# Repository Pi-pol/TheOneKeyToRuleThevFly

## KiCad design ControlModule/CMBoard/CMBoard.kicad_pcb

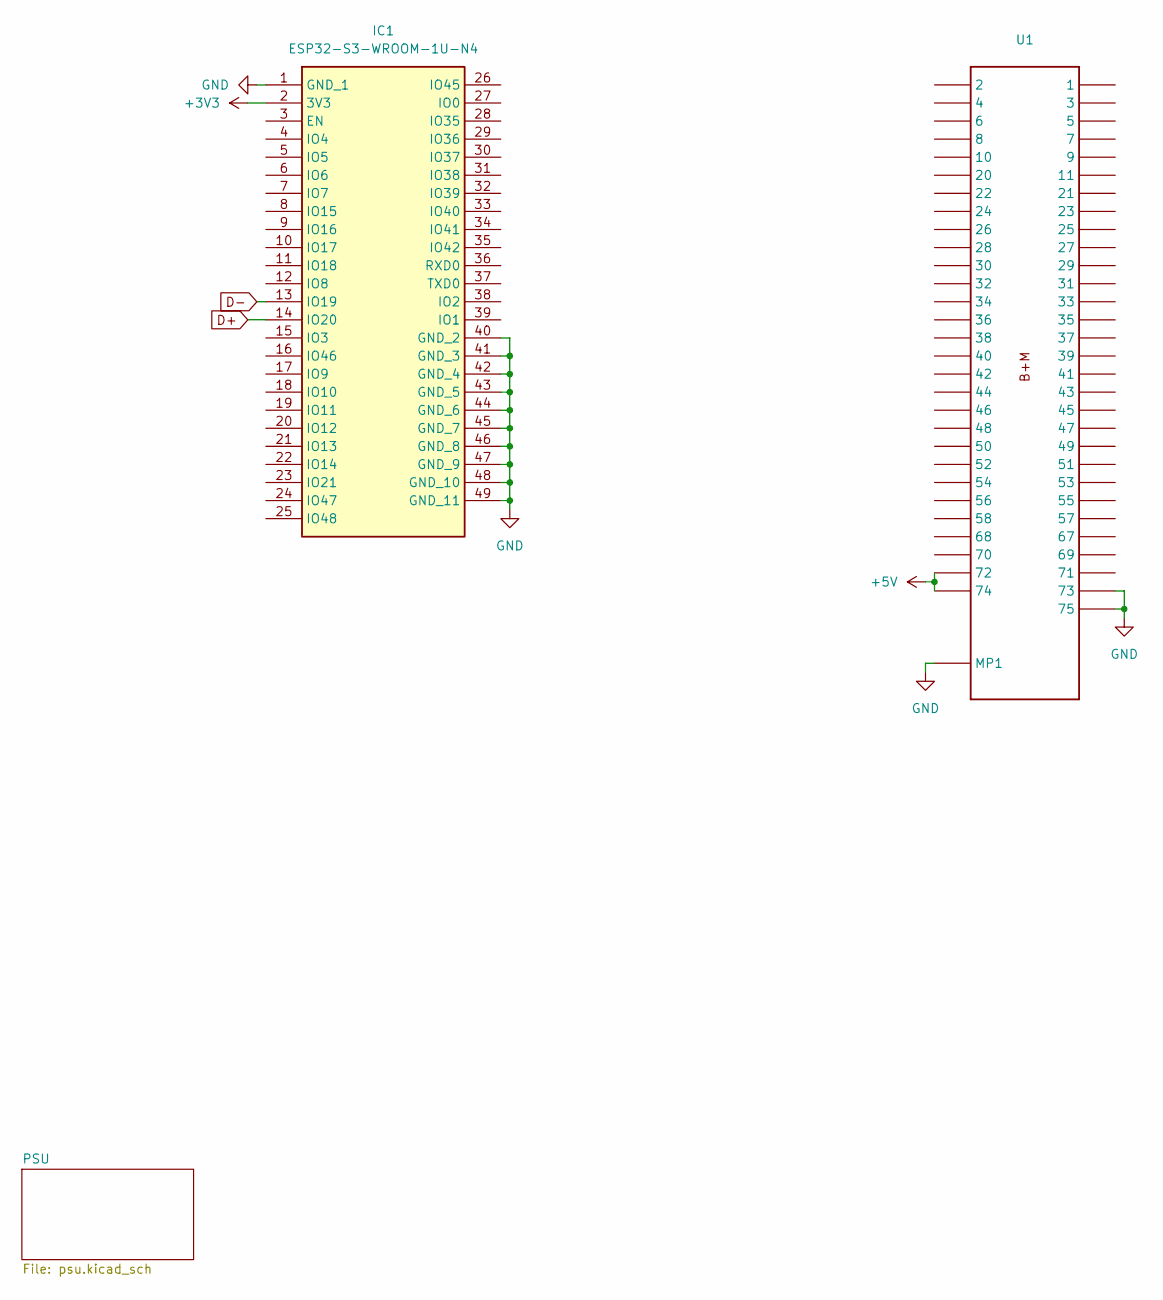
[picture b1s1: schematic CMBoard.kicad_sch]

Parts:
IC1: ESP32-S3-WROOM-1U-N4; ESP32S3WROOM1UN4; Manufacturer_Part_Number ESP32-S3-WROOM-1U-N4; Mouser Part Number 356-ESP32S3WROOM1UN4
U1: B+M 2280

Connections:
+3V3: IC1.2 (3V3); also elsewhere on the board
+5V: U1.P$72 (72), U1.P$74 (74); also elsewhere on the board
D+: IC1.14 (IO20); also elsewhere on the board
D-: IC1.13 (IO19); also elsewhere on the board
GND: IC1.1 (GND_1), IC1.40 (GND_2), IC1.41 (GND_3), IC1.42 (GND_4), IC1.43 (GND_5), IC1.44 (GND_6), IC1.45 (GND_7), IC1.46 (GND_8), IC1.47 (GND_9), IC1.48 (GND_10), IC1.49 (GND_11), U1.MP1, U1.P$73 (73), U1.P$75 (75); also elsewhere on the board

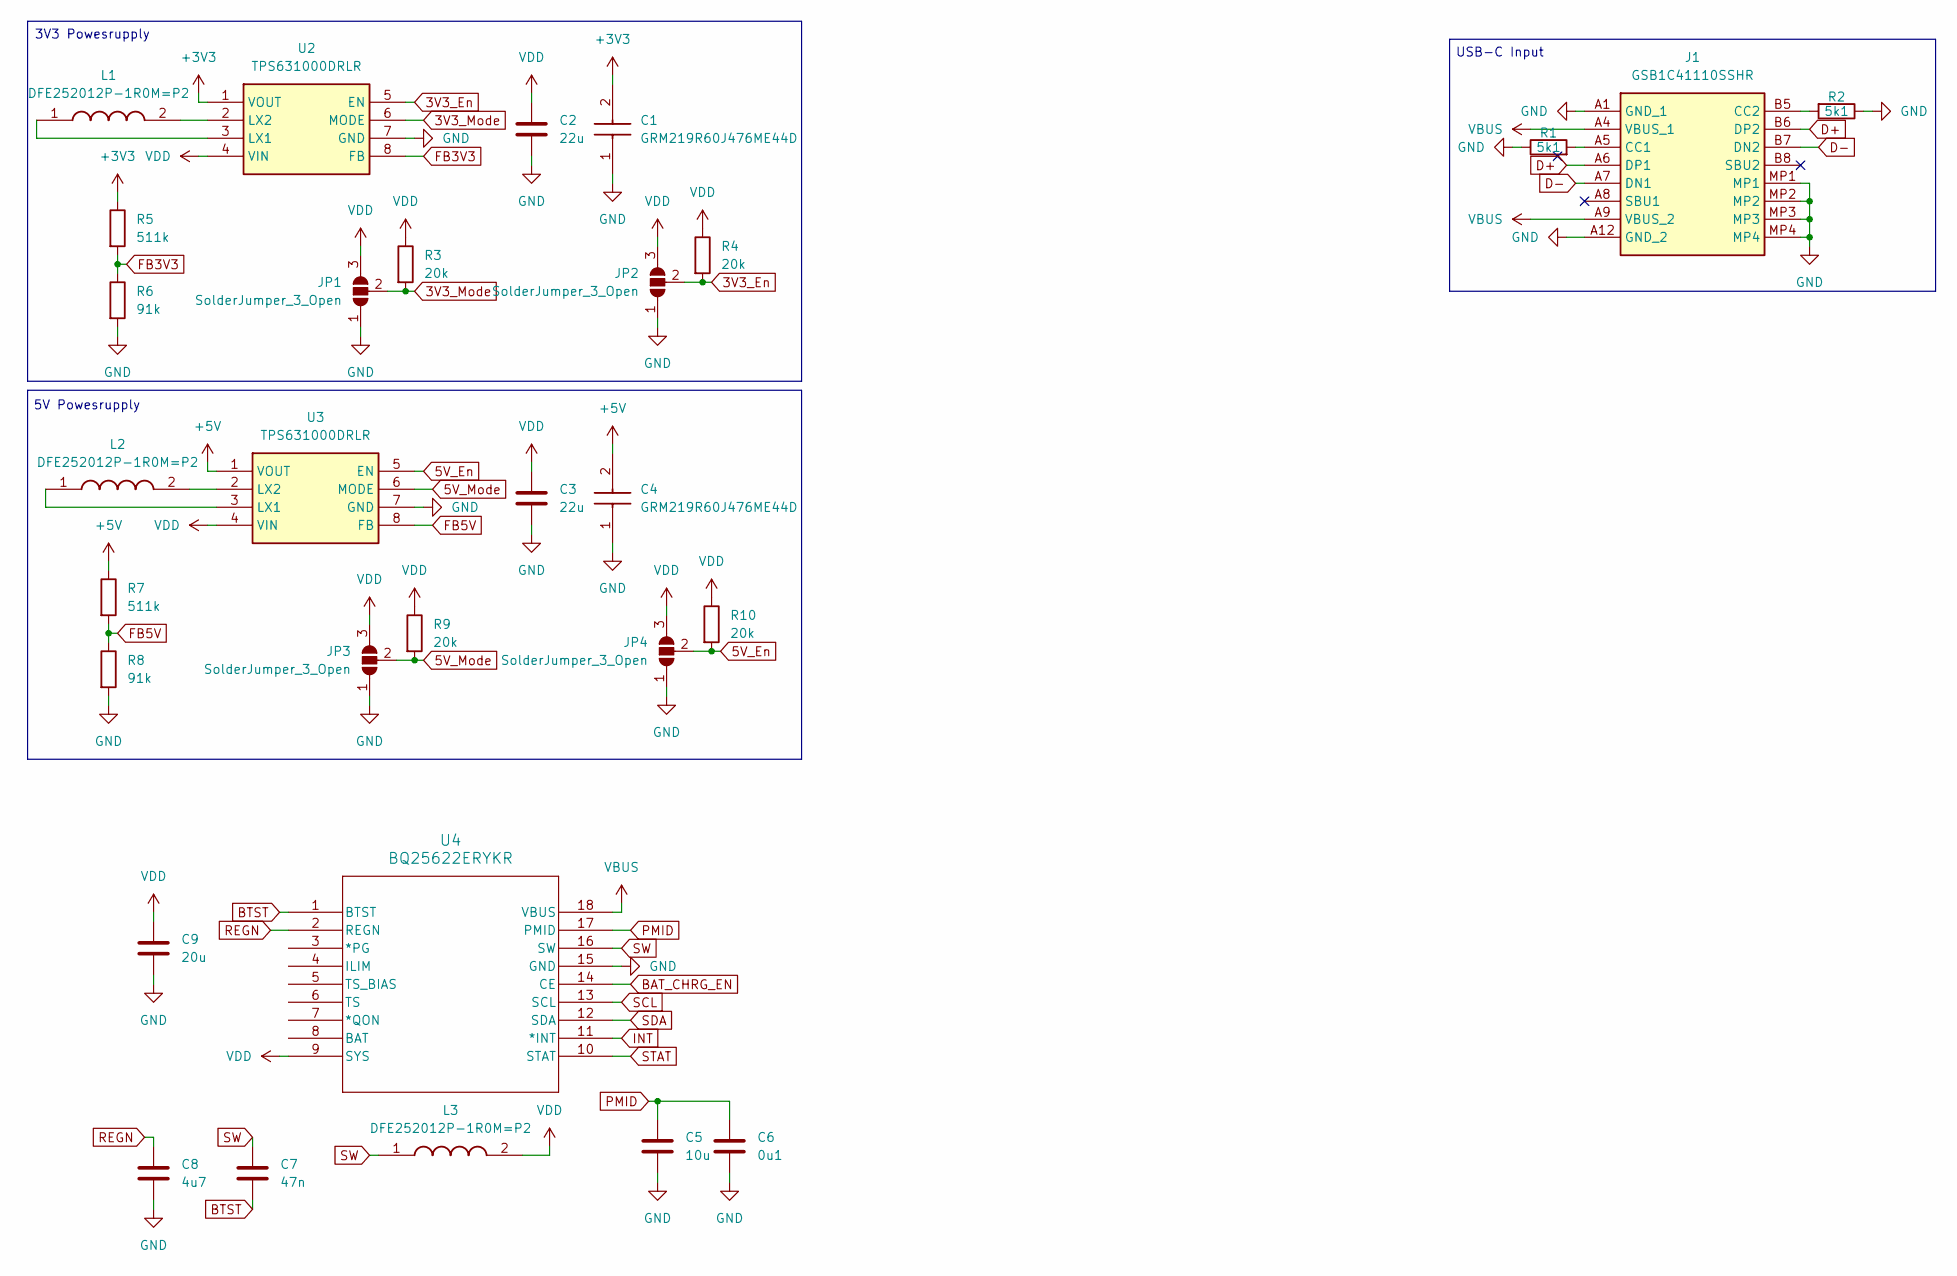
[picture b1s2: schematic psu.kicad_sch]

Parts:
C1, C4: GRM219R60J476ME44D; GRM21BR60J226ME39L; Manufacturer_Part_Number GRM219R60J476ME44D; Mouser Part Number 81-GRM219R60J476ME4D
C2, C3: 22u; C_0603_1608Metric
C5: 10u; C_0603_1608Metric
C6: 0u1; C_0603_1608Metric
C7: 47n; C_0603_1608Metric
C8: 4u7; C_0603_1608Metric
C9: 20u; C_0603_1608Metric
J1: GSB1C41110SSHR; Manufacturer_Part_Number GSB1C41110SSHR
JP1, JP2, JP3, JP4: SolderJumper_3_Open; SolderJumper-3_P1.3mm_Open_Pad1.0x1.5mm
L1, L2, L3: DFE252012P-1R0M=P2; DFE2HCAH1R0MJ0L; Manufacturer_Part_Number DFE252012P-1R0M=P2; Mouser Part Number 81-DFE252012P-1R0MP2
R1, R2: 5k1; R_0603_1608Metric
R3, R4, R9, R10: 20k; R_0603_1608Metric
R5, R7: 511k; R_0603_1608Metric
R6, R8: 91k; R_0603_1608Metric
U2, U3: TPS631000DRLR; SOTFL50P160X60-8N; Manufacturer_Part_Number TPS631000DRLR; Mouser Part Number 595-TPS631000DRLR
U4: BQ25622ERYKR; WQFN-HR18_RYK_TEX

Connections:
3V3_En: JP2.2 (C), R4.2, U2.5 (EN)
3V3_Mode: JP1.2 (C), R3.2, U2.6 (MODE)
5V_En: JP4.2 (C), R10.2, U3.5 (EN)
5V_Mode: JP3.2 (C), R9.2, U3.6 (MODE)
+3V3: C1.2, R5.1, U2.1 (VOUT); also elsewhere on the board
+5V: C4.2, R7.1, U3.1 (VOUT); also elsewhere on the board
BAT_CHRG_EN: U4.14 (CE)
BTST: C7.2, U4.1 (BTST)
D+: J1.A6 (DP1), J1.B6 (DP2); also elsewhere on the board
D-: J1.A7 (DN1), J1.B7 (DN2); also elsewhere on the board
FB3V3: R5.2, R6.1, U2.8 (FB)
FB5V: R7.2, R8.1, U3.8 (FB)
GND: C1.1, C2.2, C3.2, C4.1, C5.2, C6.2, C8.2, C9.2, J1.A1 (GND_1), J1.A12 (GND_2), J1.MP1, J1.MP2, J1.MP3, J1.MP4, JP1.1 (A), JP2.1 (A), JP3.1 (A), JP4.1 (A), R1.1, R2.1, R6.2, R8.2, U2.7 (GND), U3.7 (GND), U4.15 (GND); also elsewhere on the board
INT: U4.11 (*INT)
unnamed: J1.A5 (CC1), R1.2
unnamed: J1.B5 (CC2), R2.2
unnamed: L1.1, U2.3 (LX1)
unnamed: L1.2, U2.2 (LX2)
unnamed: L2.1, U3.3 (LX1)
unnamed: L2.2, U3.2 (LX2)
PMID: C5.1, C6.1, U4.17 (PMID)
REGN: C8.1, U4.2 (REGN)
SCL: U4.13 (SCL)
SDA: U4.12 (SDA)
STAT: U4.10 (STAT)
SW: C7.1, L3.1, U4.16 (SW)
VBUS: J1.A4 (VBUS_1), J1.A9 (VBUS_2), U4.18 (VBUS)
VDD: C2.1, C3.1, C9.1, JP1.3 (B), JP2.3 (B), JP3.3 (B), JP4.3 (B), L3.2, R3.1, R4.1, R9.1, R10.1, U2.4 (VIN), U3.4 (VIN), U4.9 (SYS)

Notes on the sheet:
5V Powesrupply
3V3 Powesrupply
USB-C Input

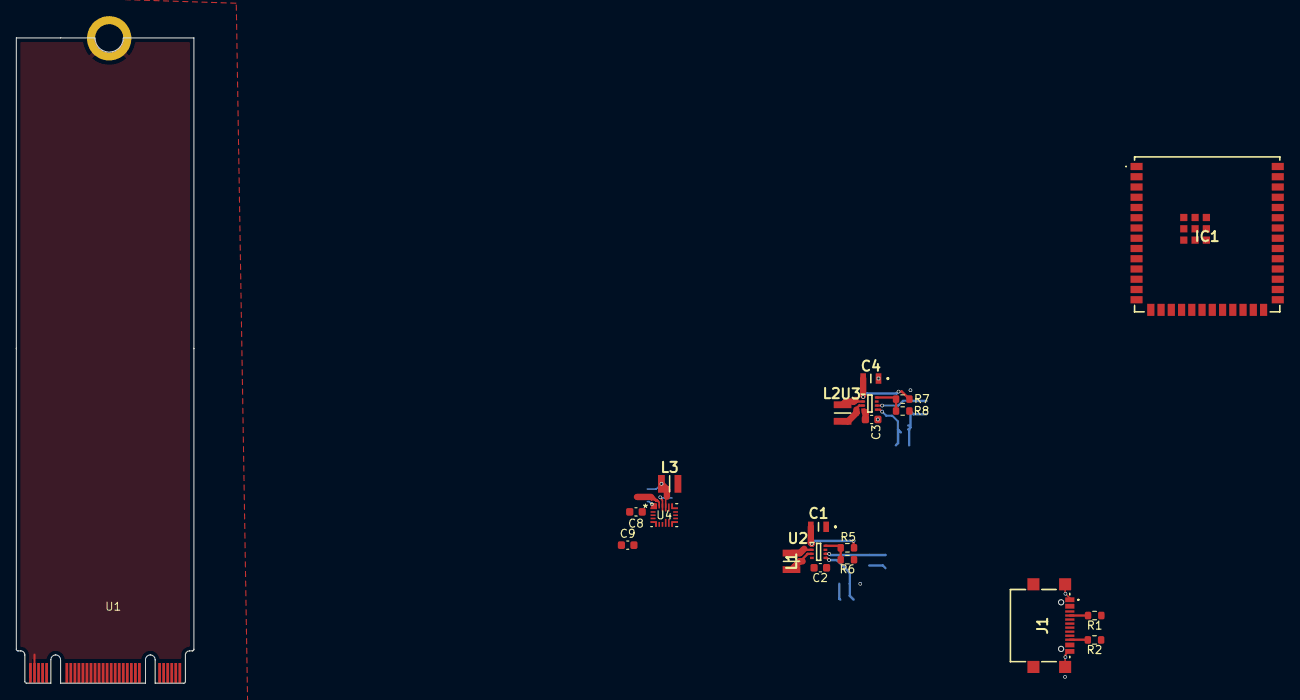
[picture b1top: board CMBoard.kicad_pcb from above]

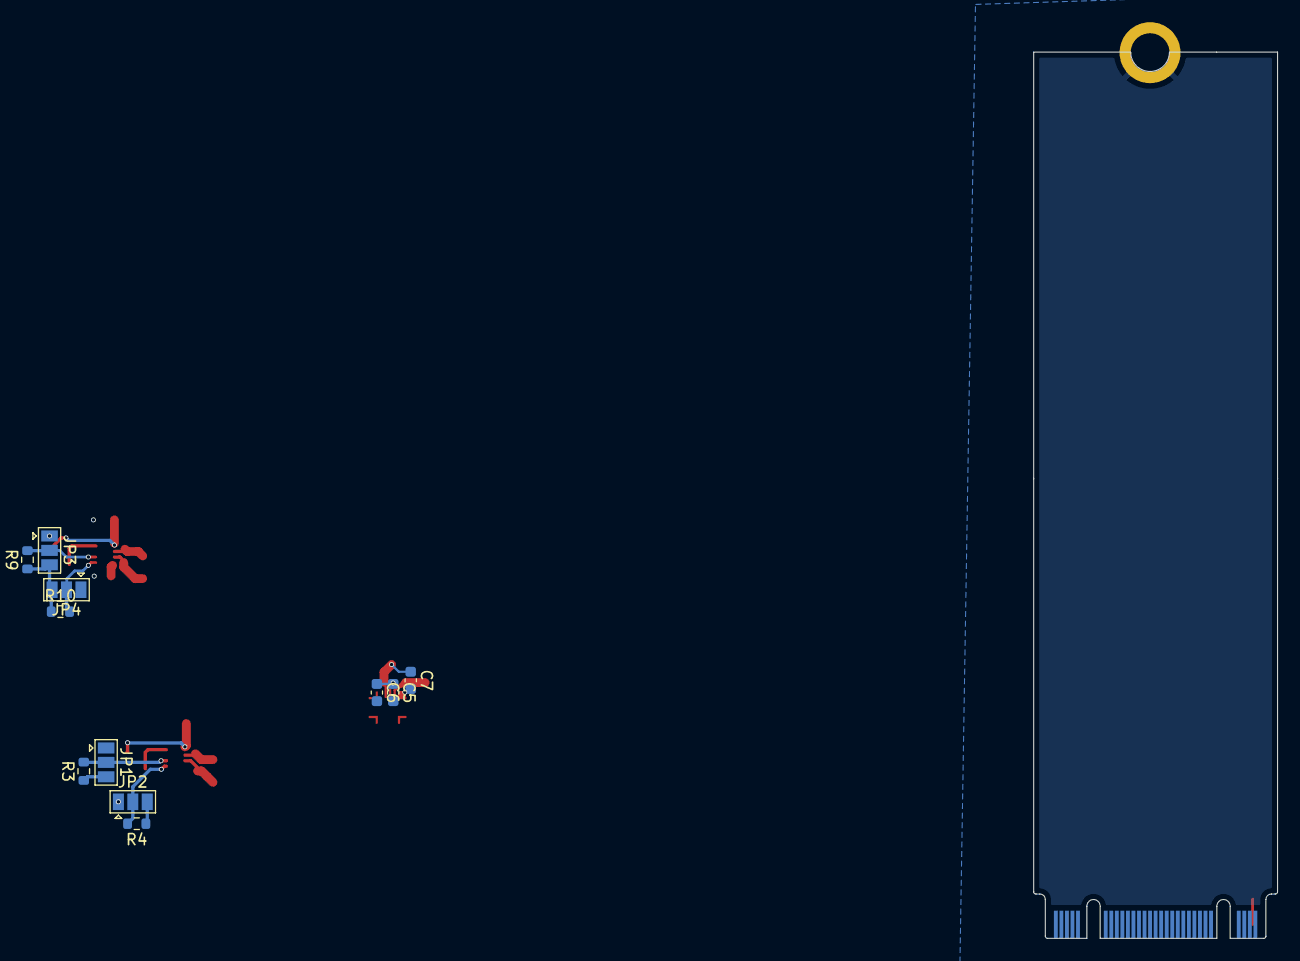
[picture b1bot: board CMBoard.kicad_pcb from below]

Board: 2 copper layers, 22.0 x 80.0 mm, 32 parts (11 on the bottom side), 23 nets.
